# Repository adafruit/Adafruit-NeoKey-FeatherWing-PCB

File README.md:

## Adafruit NeoKey FeatherWing PCB

<a href="http://www.adafruit.com/products/4979"><br/>
Click here to purchase one from the Adafruit shop</a>

PCB files for the Adafruit NeoKey FeatherWing. 

Format is EagleCAD schematic and board layout
* https://www.adafruit.com/product/4979

### Description

The only thing better than a nice mechanical key, is two of them, and ones that also can glow any color of the rainbow - and that's what the Adafruit NeoKey FeatherWing will let you do! This Wing plugs into any/all Feather main boards and can fit two Cherry MX or compatible switches to turn your Feather into the lil'est macro keypad.

Each Wing has two Kailh sockets, which means you can plug in any MX-compatible switches instead of soldering them in. You may need a little glue to keep the switches in place: hot glue or a dot of epoxy worked fine for us.

Beneath each switch is a reverse-mount NeoPixel pointing up through the spot where many switches would have an LED to shine though. The two pixels are chained together so you can control them as one 2-pixel NeoPixel strand.

We wired the switches up very simply, so you can use with any Feather. There's jumper pads you can cut to re-wire the switches and LED strand.

* Switch A - Connects to the Feather pin to the left of SCL, on most Feathers this is pin D5
* Switch B - Connects to the Feather pin two pins to the left of SCL, on most Feathers this is pin D6
* NeoPixel Input - Connects to the Feather pin three pins to the left of SCL, on most Feathers this is pin D9
* Bonus STEMMA QT connector allows you to make solderless connections between your Wing and a wide range of other sensors and accessories using a compatible cable. QT Cable is not included, but we have a variety in the shop.

Please note, each order comes with one assembled FeatherWing PCB and a two sticks of break-off header. Soldering is required to attach the header and connect to a Feather. Two mechanical switches and key caps are not included! Use any MX-compatible switch: Kailh, Gateron, etc all work.
### License

Adafruit invests time and resources providing this open source design, please support Adafruit and open-source hardware by purchasing products from [Adafruit](https://www.adafruit.com)!

Designed by Limor Fried/Ladyada for Adafruit Industries.

Creative Commons Attribution/Share-Alike, all text above must be included in any redistribution. 
See license.txt for additional details.

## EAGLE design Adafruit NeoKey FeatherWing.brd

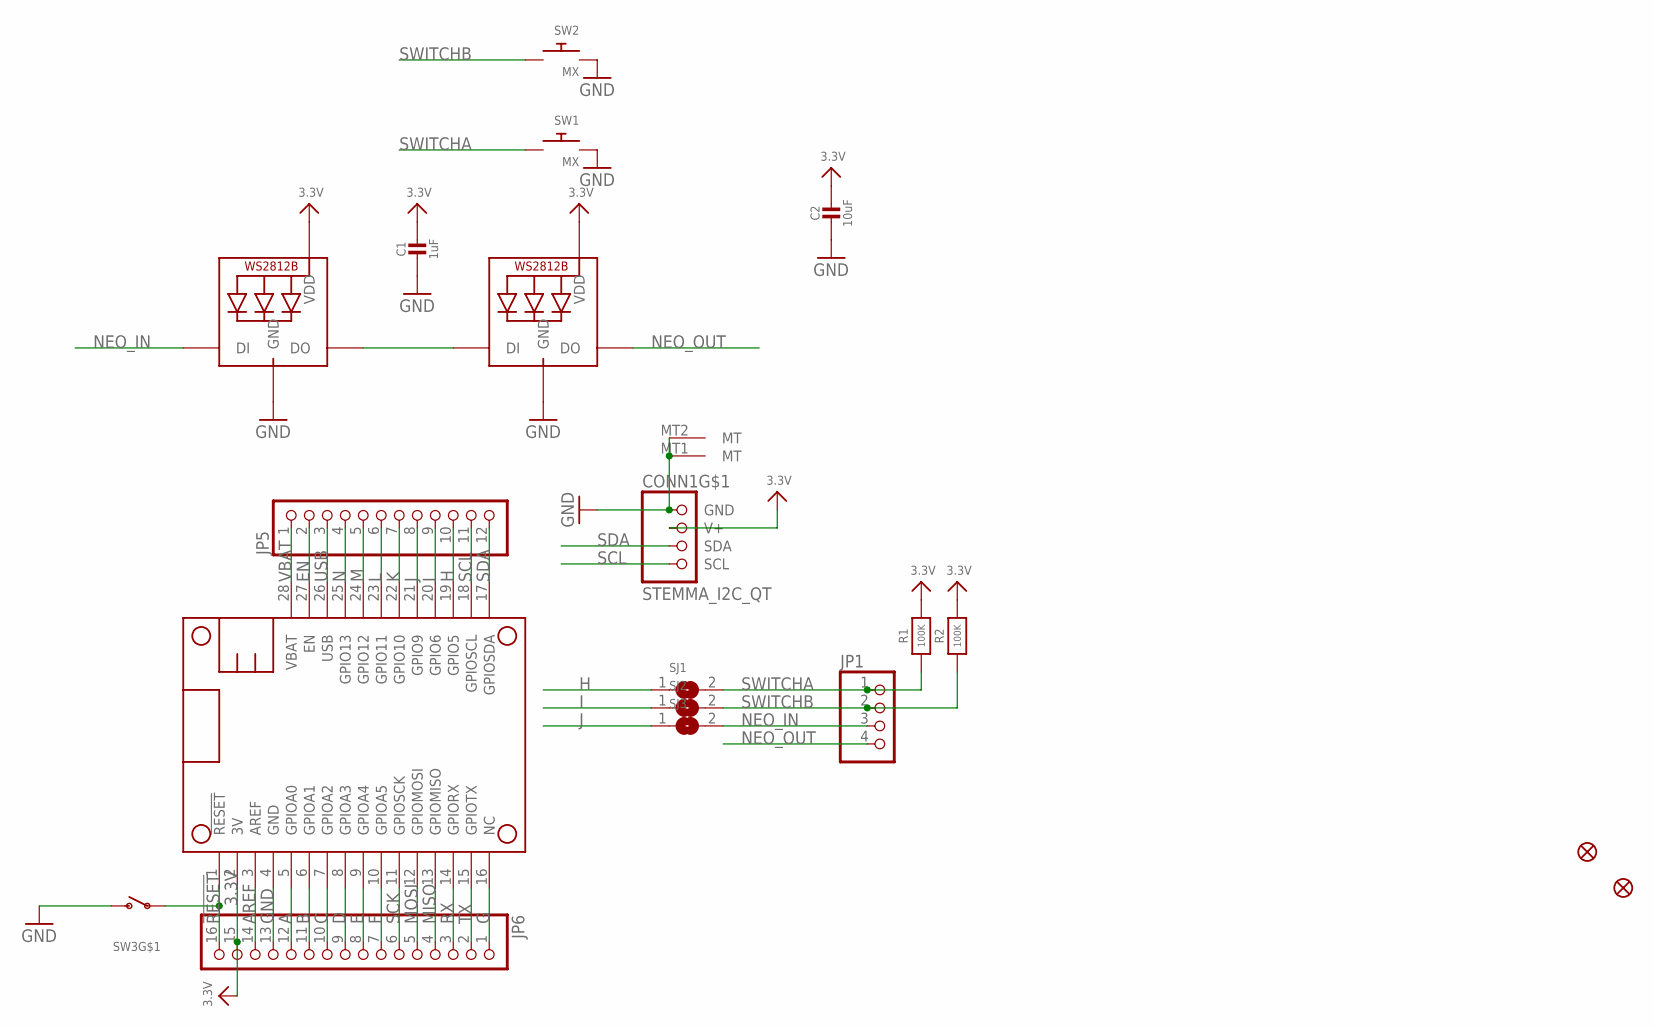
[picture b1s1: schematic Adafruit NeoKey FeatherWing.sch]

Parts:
C1: 1uF; 0603-NO
C2: 10uF; 0805-NO
CONN1: STEMMA_I2C_QT; JST_SH4
FID1, FID2: FIDUCIAL_1MM
JP1: HEADER-1X4ROUND; 1X04_ROUND
JP5: HEADER-1X12; 1X12_ROUND
JP6: HEADER-1X16ROUND; 1X16_ROUND
LED1, LED2: WS2812B_SK6812E; NEO3535_REVERSE
MS1: FEATHERWING_NODIM
R1, R2: 100K; 0603-NO
SJ1, SJ2, SJ3: SOLDERJUMPERCLOSED; SOLDERJUMPER_CLOSEDWIRE
SW1, SW2: MX; KAILH_SOCKET
SW3: SWITCH_SPST_TACT_RA; SPST_TACTILE_RA

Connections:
3.3V: C1.1, C2.1, CONN1.2 (V+), JP6.15, LED1.1-VDD (VDD), LED2.1-VDD (VDD), MS1.2 (3V), R1.2, R2.2
!RESET: JP6.16, MS1.1 (!RESET), SW3.1
A: JP6.12, MS1.5 (GPIOA0)
AREF: JP6.14, MS1.3 (AREF)
B: JP6.11, MS1.6 (GPIOA1)
C: JP6.10, MS1.7 (GPIOA2)
D: JP6.9, MS1.8 (GPIOA3)
E: JP6.8, MS1.9 (GPIOA4)
EN: JP5.2, MS1.27 (EN)
F: JP6.7, MS1.10 (GPIOA5)
G: JP6.1, MS1.16 (NC)
GND: C1.2, C2.2, CONN1.1 (GND), CONN1.MT1 (MT), CONN1.MT2 (MT), JP6.13, LED1.3-GND (GND), LED2.3-GND (GND), MS1.4 (GND), SW1.1, SW2.1, SW3.2 (S)
H: JP5.10, MS1.19 (GPIO5), SJ1.1
I: JP5.9, MS1.20 (GPIO6), SJ2.1
J: JP5.8, MS1.21 (GPIO9), SJ3.1
K: JP5.7, MS1.22 (GPIO10)
L: JP5.6, MS1.23 (GPIO11)
M: JP5.5, MS1.24 (GPIO12)
MISO: JP6.4, MS1.13 (GPIOMISO)
MOSI: JP6.5, MS1.12 (GPIOMOSI)
N: JP5.4, MS1.25 (GPIO13)
unnamed: LED1.4-DIN (DI), LED2.2-DOUT (DO)
NEO_IN: JP1.3, LED2.4-DIN (DI), SJ3.2
NEO_OUT: JP1.4, LED1.2-DOUT (DO)
RX: JP6.3, MS1.14 (GPIORX)
SCK: JP6.6, MS1.11 (GPIOSCK)
SCL: CONN1.4 (SCL), JP5.11, MS1.18 (GPIOSCL)
SDA: CONN1.3 (SDA), JP5.12, MS1.17 (GPIOSDA)
SWITCHA: JP1.1, R1.1, SJ1.2, SW1.2
SWITCHB: JP1.2, R2.1, SJ2.2, SW2.2
TX: JP6.2, MS1.15 (GPIOTX)
USB: JP5.3, MS1.26 (USB)
VBAT: JP5.1, MS1.28 (VBAT)

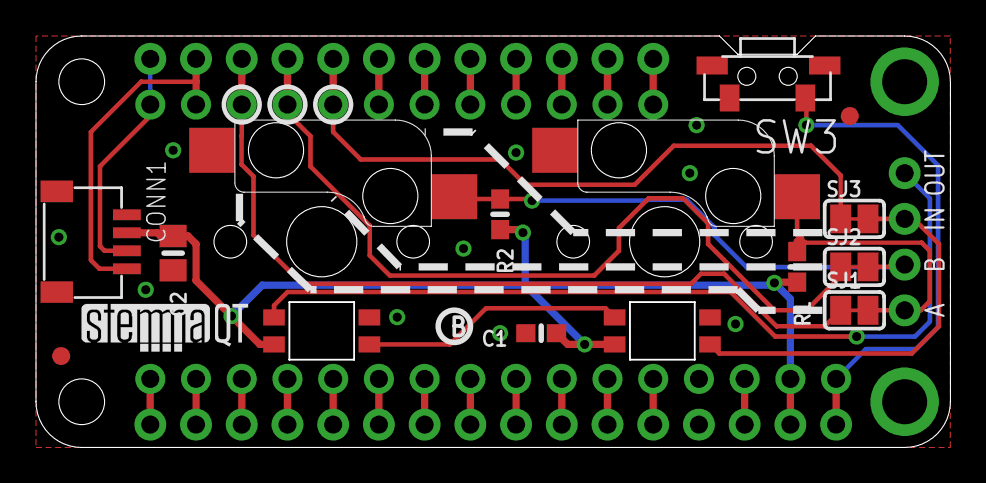
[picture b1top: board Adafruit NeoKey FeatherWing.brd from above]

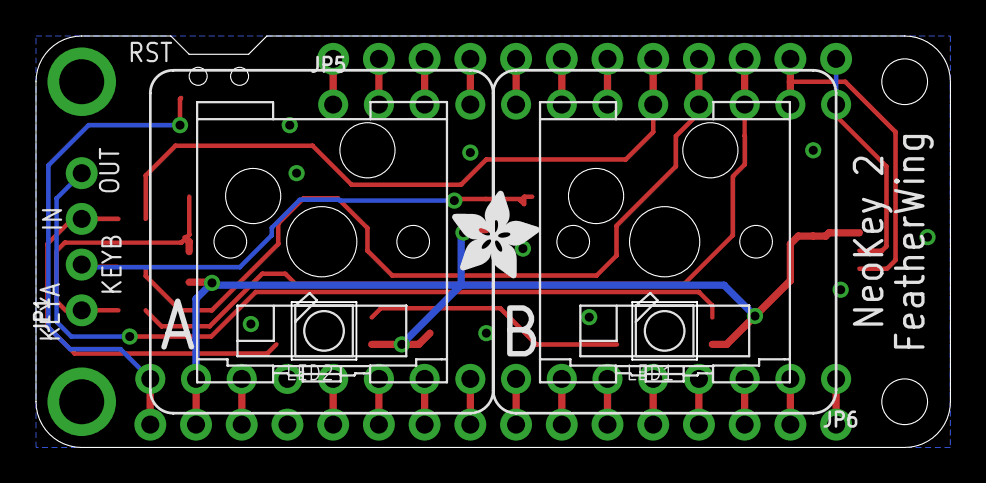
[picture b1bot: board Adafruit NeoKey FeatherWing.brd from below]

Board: 2 copper layers, 50.7 x 22.8 mm, 22 parts (9 on the bottom side), 33 nets.

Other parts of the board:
U$7: ADAFRUIT_5MM
U$8: PCBFEAT-REV-040
U$11: STEMMAQT

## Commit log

2021-04-20 Adding board files.

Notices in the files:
parts and their libraries:
microbuilder: This work is placed in the public domain, and may be freely used for commercial and non-commercial work with the following conditions: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
